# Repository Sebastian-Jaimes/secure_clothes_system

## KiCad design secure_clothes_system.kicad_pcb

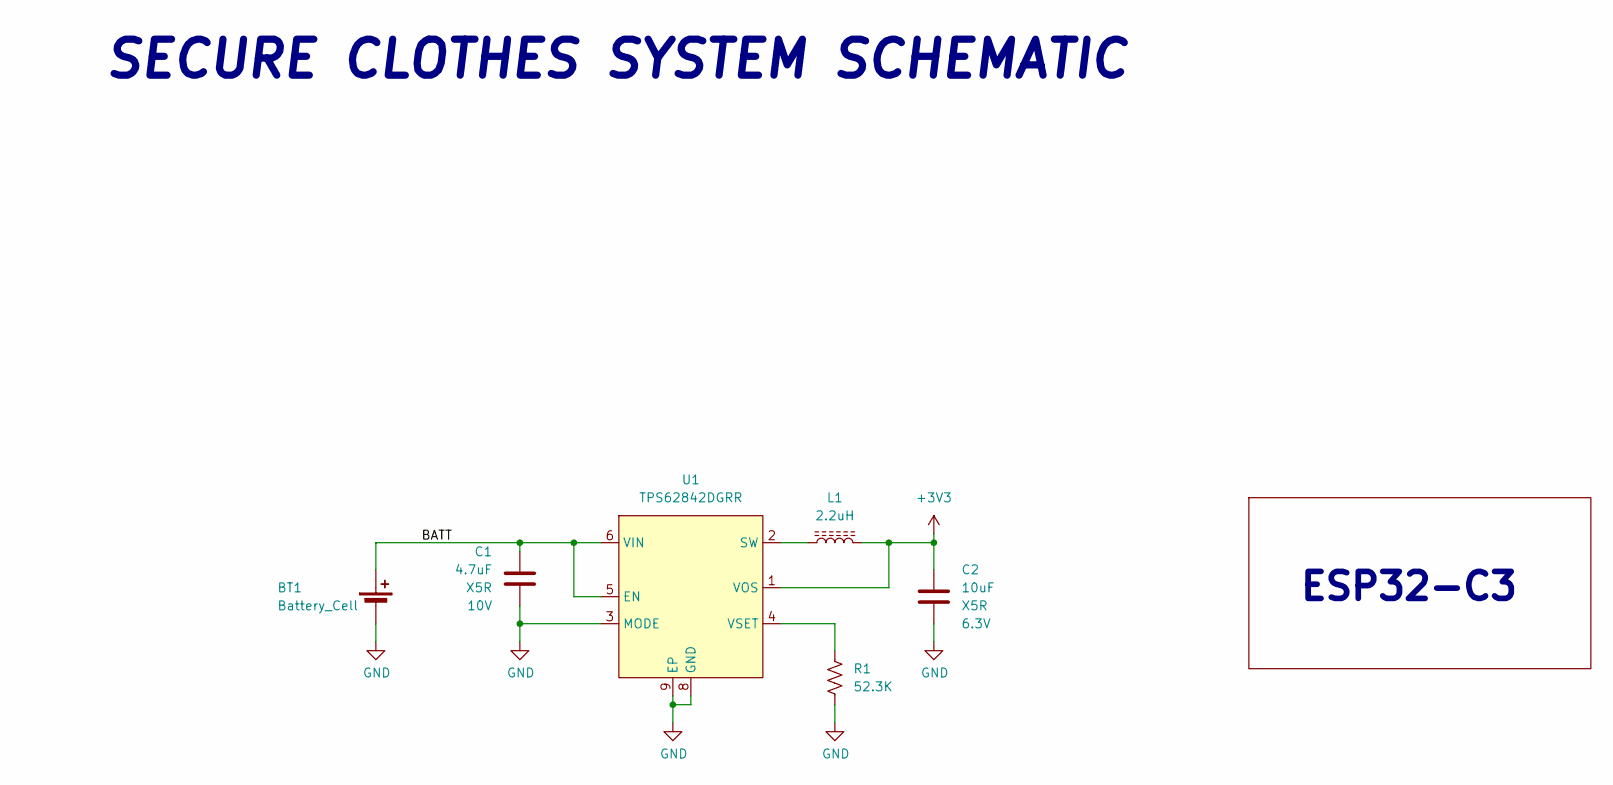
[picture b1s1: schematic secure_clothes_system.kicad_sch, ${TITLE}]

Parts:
BT1: Battery_Cell; PinHeader_1x02_P2.00mm_Vertical
C1: 4.7uF; C_0402_1005Metric; VOLTAGE 10V; Mfg Part # CL05A475MP5NRNC
C2: 10uF; C_0402_1005Metric; VOLTAGE 6.3V; Mfg Part # GRM155R60J106ME15D
L1: 2.2uH; L_Murata_DFE201610P; Mfg Part # DFE201612E-2R2M=P2
R1: 52.3K; R_0402_1005Metric; Mfg Part # RC0402FR-0752K3L
U1: TPS62842DGRR; HVSSOP-8-1EP_3x3mm_P0.65mm_EP1.57x1.89mm_ThermalVias; Mfg Part # TPS62842DGRR

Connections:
+3V3: C2.1, L1.2, U1.1 (VOS); also elsewhere on the board
/BATT: BT1.1 (+), C1.1, U1.5 (EN), U1.6 (VIN)
GND: BT1.2 (-), C1.2, C2.2, R1.2, U1.3 (MODE), U1.8 (GND), U1.9 (EP); also elsewhere on the board
unnamed: L1.1, U1.2 (SW)
unnamed: R1.1, U1.4 (VSET)

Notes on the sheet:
SECURE CLOTHES SYSTEM SCHEMATIC
ESP32-C3

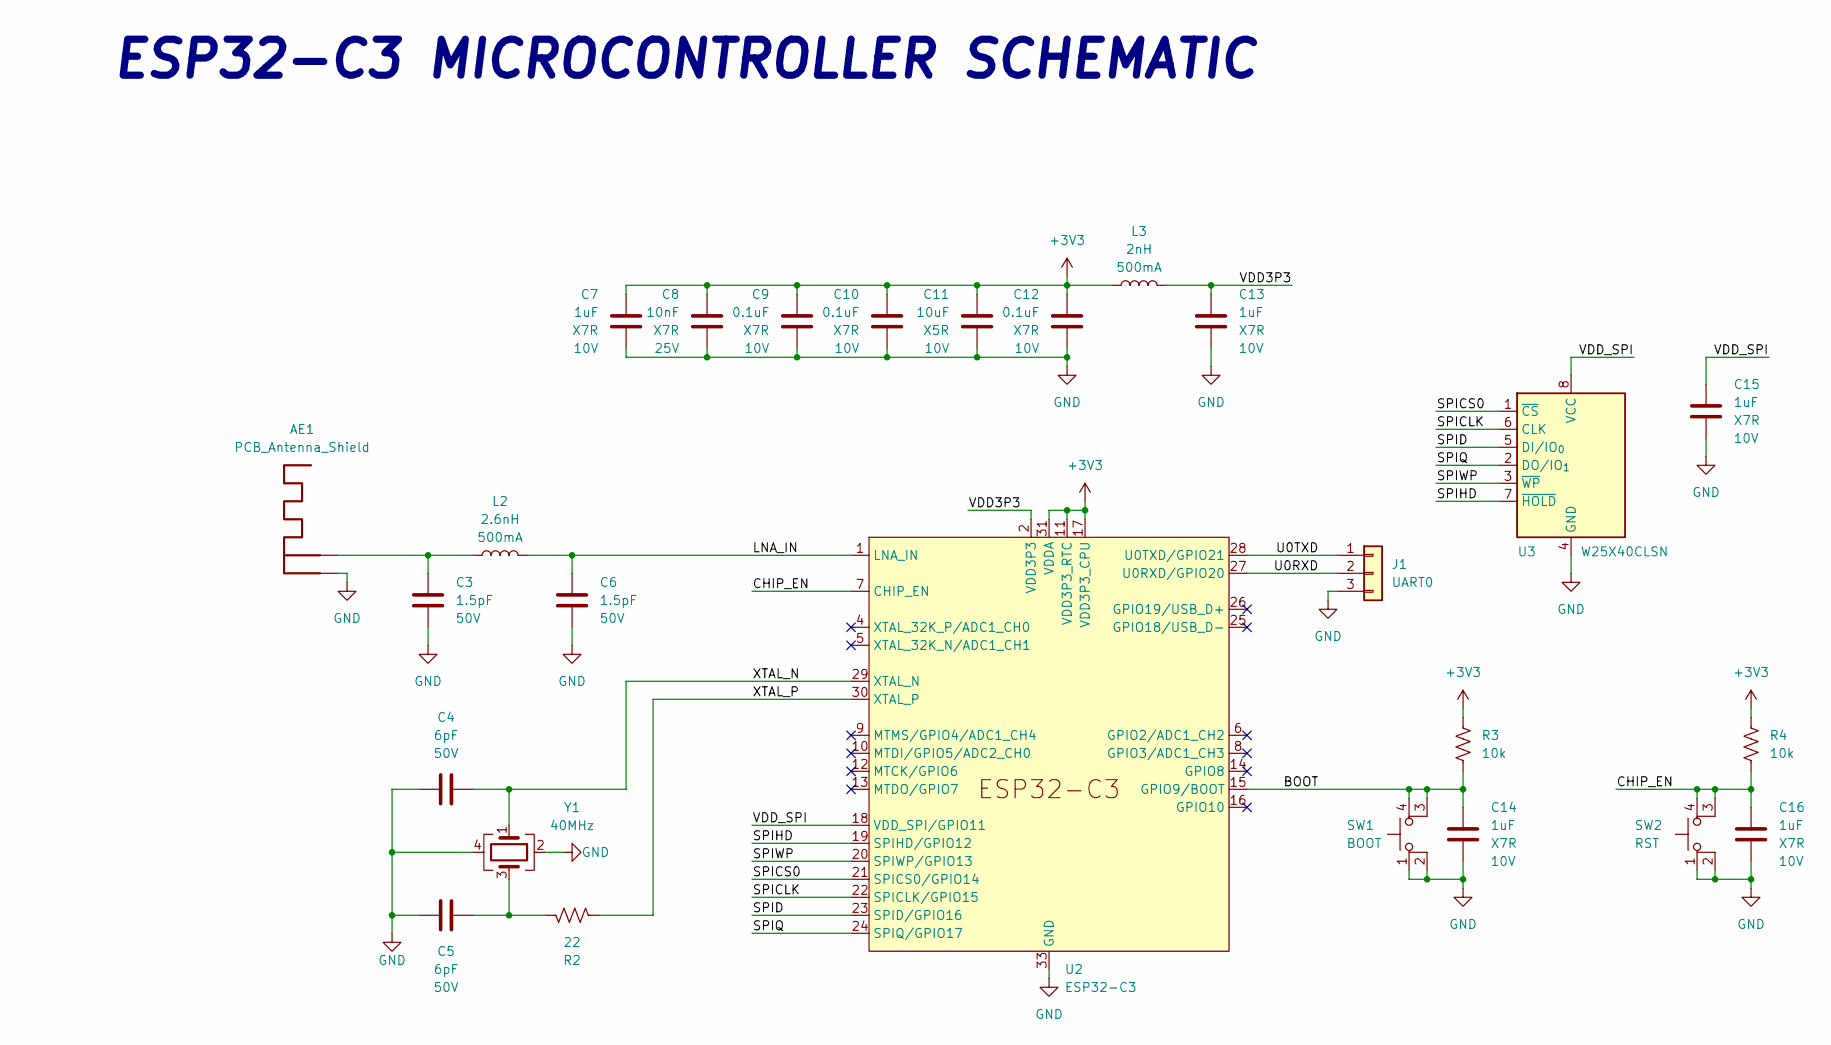
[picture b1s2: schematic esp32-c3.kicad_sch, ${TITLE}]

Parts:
AE1: PCB_Antenna_Shield; Texas_SWRA117D_2.4GHz_Left
C3, C6: 1.5pF; C_0201_0603Metric; Voltage 50V; Mfg Part # GRM0335C1H1R5BA01D
C4, C5: 6pF; C_0402_1005Metric; Voltage 50V; Mfg Part # CC0402BRNPO9BN6R0
C7, C13, C14, C15, C16: 1uF; C_0402_1005Metric; Voltage 10V; Mfg Part # GRM155Z71A105KE01D
C8: 10nF; C_0402_1005Metric; Voltage 25V; Mfg Part # C0402C103K3REC7411
C9, C10, C12: 0.1uF; C_0402_1005Metric; Voltage 10V; Mfg Part # CL05B104KP5NNNC
C11: 10uF; C_0402_1005Metric; Voltage 10V; Mfg Part # GRM155R61A106ME11D
J1: UART0; PinHeader_1x03_P2.00mm_Vertical
L2: 2.6nH; L_0201_0603Metric; Mfg Part # LQP03TN2N6B02D
L3: 2nH; L_0201_0603Metric; Mfg Part # ATFC-0201HQ-2N0B-T
R2: 22; R_0402_1005Metric; Mfg Part # ERJ-2RKF22R0X
R3, R4: 10k; R_0402_1005Metric; Mfg Part # ERJ-2RKF1002X
SW1: BOOT; SW_SPST_PTS815; Mfg Part # PTS815SJG250SMTR LFS
SW2: RST; SW_SPST_PTS815; Mfg Part # PTS815SJG250SMTR LFS
U2: ESP32-C3; QFN-32-1EP_5x5mm_P0.5mm_EP3.45x3.45mm; Mfg Part # ESP32-C3
U3: W25X40CLSN; SOIC-8_3.9x4.9mm_P1.27mm; Mfg Part # W25X40CLSNIG
Y1: 40MHz; Crystal_SMD_3225-4Pin_3.2x2.5mm; Mfg Part # RH100-40.000-6-F-1010-TR-NS1

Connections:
+3V3: C7.1, C8.1, C9.1, C10.1, C11.1, C12.1, L3.1, R3.1, R4.1, U2.11 (VDD3P3_RTC), U2.17 (VDD3P3_CPU), U2.31 (VDDA), U2.32 (VDDA); also elsewhere on the board
/ESP32-C3/BOOT: C14.1, R3.2, SW1.3 (K), SW1.4 (A), U2.15 (GPIO9/BOOT)
/ESP32-C3/CHIP_EN: C16.1, R4.2, SW2.3 (K), SW2.4 (A), U2.7 (CHIP_EN)
/ESP32-C3/LNA_IN: C6.1, L2.2, U2.1 (LNA_IN)
/ESP32-C3/SPICLK: U2.22 (SPICLK/GPIO15), U3.6 (CLK)
/ESP32-C3/SPICS0: U2.21 (SPICS0/GPIO14), U3.1 (~CS)
/ESP32-C3/SPID: U2.23 (SPID/GPIO16), U3.5 (DI/IO_{0})
/ESP32-C3/SPIHD: U2.19 (SPIHD/GPIO12), U3.7 (~HOLD)
/ESP32-C3/SPIQ: U2.24 (SPIQ/GPIO17), U3.2 (DO/IO_{1})
/ESP32-C3/SPIWP: U2.20 (SPIWP/GPIO13), U3.3 (~WP)
/ESP32-C3/U0RXD: J1.2, U2.27 (U0RXD/GPIO20)
/ESP32-C3/U0TXD: J1.1, U2.28 (U0TXD/GPIO21)
/ESP32-C3/VDD3P3: C13.1, L3.2, U2.2 (VDD3P3), U2.3 (VDD3P3)
/ESP32-C3/VDD_SPI: C15.1, U2.18 (VDD_SPI/GPIO11), U3.8 (VCC)
/ESP32-C3/XTAL_N: C4.2, U2.29 (XTAL_N), Y1.1
/ESP32-C3/XTAL_P: R2.2, U2.30 (XTAL_P)
GND: AE1.2 (Shield), C3.2, C4.1, C5.1, C6.2, C7.2, C8.2, C9.2, C10.2, C11.2, C12.2, C13.2, C14.2, C15.2, C16.2, J1.3, SW1.1, SW1.2, SW2.1, SW2.2, U2.33 (GND), U3.4 (GND), Y1.2, Y1.4; also elsewhere on the board
unnamed: AE1.1 (A), C3.1, L2.1
unnamed: C5.2, R2.1, Y1.3

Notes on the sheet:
ESP32-C3 MICROCONTROLLER SCHEMATIC

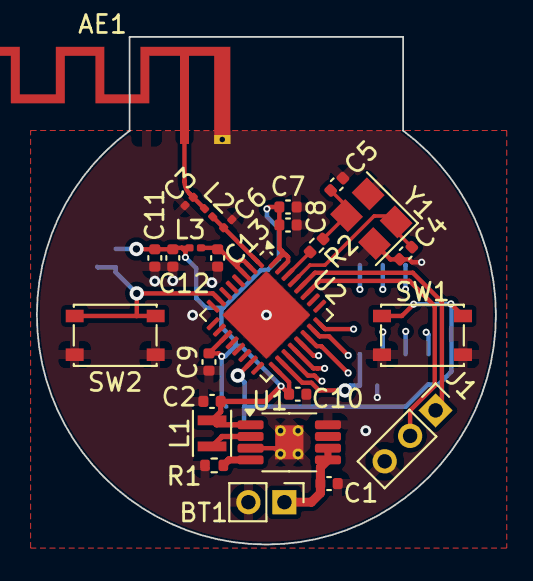
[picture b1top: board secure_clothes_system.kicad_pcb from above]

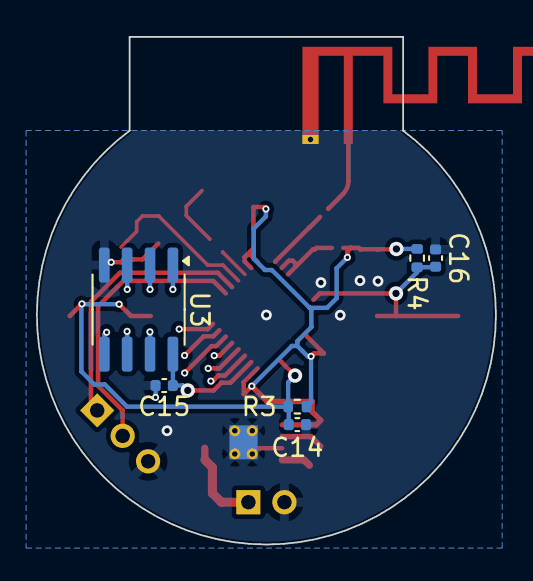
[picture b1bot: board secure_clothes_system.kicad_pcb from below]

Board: 4 copper layers, 25.5 x 28.2 mm, 32 parts (6 on the bottom side), 22 nets.

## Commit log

2024-12-11 First version of the schematic done
2024-12-12 Made the components quote and found some alternatives for the MCU
2024-12-16 Made the components quote with the alternative ESP32-C3
2024-12-18 Made the first version of the layout with the ESP32-C3
2025-01-02 Made some fixes with the layout
2025-01-04 Made the first version of the layout - DRC OK
2025-09-09 Made some fixes.
2025-09-16 Solved some warnings
2025-09-20 Fabrication.kicad_jobset added.
